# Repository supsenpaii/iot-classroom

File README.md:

# SmartClass

Giáo viên chiếu câu hỏi, học sinh bấm đáp án trên thiết bị ESP32-C3. Đáp án đi qua Wi-Fi/WebSocket, được lưu vào SQLite rồi máy chủ mới trả ACK, nên kết quả hiện lên web ngay lập tức.

<table>
<tr>
<td width="38%" valign="top">

**Nội dung**

1. [Kiến trúc hệ thống](#1-kiến-trúc-hệ-thống)
2. [Phần cứng](#2-phần-cứng)
   - [Linh kiện](#21-linh-kiện)
   - [Sơ đồ nguyên lý](#22-sơ-đồ-nguyên-lý)
   - [Mạch in PCB](#23-mạch-in-pcb)
   - [Mô hình 3D](#24-mô-hình-3d)
   - [Gán chân](#25-gán-chân)
   - [File thiết kế](#26-file-thiết-kế)
3. [Firmware ESP32](#3-firmware-esp32)
4. [Phần mềm Web](#4-phần-mềm-web)
5. [Giao thức & độ tin cậy](#5-giao-thức--độ-tin-cậy)
6. [Cài đặt & chạy](#6-cài-đặt--chạy)

</td>
<td width="62%" valign="top">

<p align="center"><sub>Thiết bị học sinh: ESP32-C3, PCB 2 lớp 50 × 80 mm, 13 phím, OLED 0,91"</sub></p>
</td>
</tr>
</table>

---

## 1. Kiến trúc hệ thống

| Thành phần | Công nghệ | Vai trò |
|---|---|---|
| Thiết bị học sinh | ESP32-C3-MINI-1-N4, bàn phím, OLED SSD1306 | Nhập ROOM ID + MSSV, gửi đáp án, hiện trạng thái |
| Backend | Node.js 24, Express 5, `ws` 8, SQLite (better-sqlite3) | Kiểm tra → lưu → ACK, máy trạng thái buổi thi |
| Frontend | React 19, Vite 8 | Bảng giáo viên, màn chiếu, báo cáo, `/student`, `/device` |
| AI ôn tập | Gemini (chính), OpenRouter (dự phòng) | Giải thích câu sai, sinh câu luyện thêm |

Học sinh không có thiết bị vẫn tham gia được bằng điện thoại qua `/student`, hoặc thiết bị ảo `/device`. Mọi nguồn đều dùng chung một đường WebSocket và một bộ luật chấm.

---

## 2. Phần cứng

PCB 2 lớp FR-4 1,6 mm, kích thước **50 × 80 mm**, 57 vị trí linh kiện, toàn bộ linh kiện ở mặt trên. ERC và DRC đều **0 lỗi**. Có 431 đoạn dây và 64 via. Dưới module ESP32 có 9 via tản nhiệt, cả hai mặt đổ đồng GND, chừa vùng cấm đồng dưới anten.

### 2.1 Linh kiện

| Khối | Linh kiện chính | Ghi chú |
|---|---|---|
| MCU | **ESP32-C3-MINI-1-N4** | RISC-V 160 MHz, Wi-Fi 2,4 GHz, BLE 5.0, flash 4 MB, anten PCB; USB Serial/JTAG có sẵn |
| Nguồn | 4 × AAA → **AMS1117-3.3** | Vin ≥ 4,3 V khi Wi-Fi phát (đỉnh ~350–400 mA) |
| Chọn nguồn / bảo vệ | **AO3401A** (P-MOS), **SS14**, **USBLC6-2SC6** | Chống ngược pin, tự ngắt pin khi cắm USB, chống ESD cho D+/D− |
| Giao tiếp | 13 phím 6×6 (0–9, OK, DEL, MODE), RESET/BOOT, SW1 MSS-22D18G2 | OLED 0,91" I²C qua header J3 |
| Báo hiệu | 3 LED 0805: nguồn / trạng thái / USB | Thụ động 0805 cho dễ hàn tay |

BOM đầy đủ: [`hardware/fabrication/IOT_BOM_V2.csv`](hardware/fabrication/IOT_BOM_V2.csv) (57 vị trí, cần mua 51 linh kiện).

### 2.2 Sơ đồ nguyên lý

<table>
<tr>
<td width="50%"><br><b>① Nguồn vào & bảo vệ.</b> Pin → SW1 → Q1 → VSYS. Cực G của Q1 nối VBUS: cắm USB thì Q1 ngắt, nguồn đi qua D1.</td>
<td width="50%"><br><b>② Ổn áp 3,3 V.</b> AMS1117-3.3. Ngõ ra dùng tụ tantalum 22 µF (cần ESR đủ lớn để LDO ổn định). LED D2 báo nguồn.</td>
</tr>
<tr>
<td><br><b>③ USB-C.</b> CC1/CC2 qua 5,1 kΩ; D+/D− qua 22 Ω và USBLC6 tới IO19/IO18 để nạp firmware và xem log.</td>
<td><br><b>④ MCU.</b> EN có RC 10 kΩ / 1 µF + nút RESET; IO9 + nút BOOT. Chân strapping IO2, IO8 được kéo lên.</td>
</tr>
<tr>
<td><br><b>⑤ Bàn phím.</b> Ma trận 4 hàng × 3 cột cho 12 phím, MODE nối riêng → 13 phím chỉ tốn 8 GPIO.</td>
<td><br><b>⑥ OLED / LED / đo pin.</b> I²C IO4/IO5 kéo lên 4,7 kΩ; LED trạng thái IO8; cầu chia 200k/100k đưa vào ADC IO3.</td>
</tr>
</table>

### 2.3 Mạch in PCB

<table>
<tr>
<td align="center" width="25%"><br><sub>F.Cu + in lụa</sub></td>
<td align="center" width="25%"><br><sub>B.Cu (lật gương)</sub></td>
<td align="center" width="25%"><br><sub>Đi dây 2 lớp</sub></td>
<td align="center" width="25%"><br><sub>Bản vẽ lắp ráp</sub></td>
</tr>
</table>

<p align="center"><br><sub>Kích thước mạch (mm): bo góc R4, lỗ M3 cách mép 4 mm</sub></p>

Thông số đi dây: tín hiệu 0,25 mm, nguồn 0,4–0,5 mm, chân ESP32/USB 0,2 mm; khe hở tối thiểu 0,2 mm; via 0,6/0,3 mm. Thông số đặt xưởng: 2 lớp, đồng 1 oz, mạ **ENIG**, phủ xanh chữ trắng, kèm stencil.

### 2.4 Mô hình 3D

<table>
<tr>
<td align="center" width="50%"><br><sub>Mặt trên</sub></td>
<td align="center" width="50%"><br><sub>Mặt dưới, có logo HCMUTE</sub></td>
</tr>
<tr>
<td align="center"><br><sub>ESP32-C3, AMS1117, header OLED</sub></td>
<td align="center"><br><sub>RESET/BOOT, công tắc SW1, USB-C</sub></td>
</tr>
</table>

### 2.5 Gán chân

Firmware hiện chạy trên **bản mẫu** (bo ESP32-C3 cắm USB + bàn phím 4×4 rời). Muốn dùng cho mạch PCB thì phải đổi bảng chân:

| Chức năng | Bản mẫu (firmware hiện tại) | Mạch PCB |
|---|---|---|
| Bàn phím | 4×4: hàng GPIO9, 10, 20, 21 · cột GPIO8, 7, 6, 5 | 4×3 + MODE: hàng IO0, IO1, IO2, IO10 · cột IO6, IO7, IO21 · MODE IO20 |
| Phím A–D | Phím riêng | MODE chuyển sang chế độ chữ |
| OLED I²C | SDA GPIO0, SCL GPIO1 | SDA IO4, SCL IO5 (kéo lên 4,7 kΩ) |
| LED / đo pin | — | LED IO8 · ADC IO3 |
| Nguồn | USB | 4×AAA hoặc USB-C |

### 2.6 File thiết kế

```
hardware/
├── kicad/                 # Project KiCad 10: mở IOT.kicad_pro
│   ├── IOT.kicad_sch / IOT.kicad_pcb / IOT.kicad_sym
│   ├── IOT.pretty/        # footprint riêng (ESP32-C3-MINI-1, MSS-22D18G2, nút 3×4)
│   └── 3dmodels/          # STEP (đường dẫn ${KIPRJMOD})
├── fabrication/           # Gerber .zip, BOM .csv/.xlsx, sơ đồ lắp ráp, bản in 1:1, hướng dẫn đặt mạch
└── Schematic_PCB.pdf      # Ảnh chi tiết sơ đồ, PCB, 3D (7 trang)
```

---

## 3. Firmware ESP32

`firmware/esp32-classroom/`: PlatformIO + Arduino, board `esp32-c3-devkitm-1`, USB CDC. Thư viện: ArduinoWebsockets, ArduinoJson 7, Adafruit SSD1306, Preferences (NVS).

```bash
cp firmware/esp32-classroom/include/device_config.example.h firmware/esp32-classroom/include/device_config.h
# điền Wi-Fi, DEVICE_ID/SECRET (lấy ở web: Thiết bị → Đăng ký), WS_HOST = IP máy chạy backend
pio run -d firmware/esp32-classroom -t upload
pio device monitor -d firmware/esp32-classroom
```

| Trạng thái OLED | Ý nghĩa |
|---|---|
| `ROOM ID + ENTER` → `STUDENT ID + ENTER` | Nhập mã phòng 8 số, rồi MSSV (1–10 số) |
| `READY / WAITING` | Đã ghép, chờ giáo viên bắt đầu |
| `QUIZ IN PROGRESS · Q 2/10 10s` | Đếm ngược theo giờ máy chủ |
| `SENDING: A` → `SAVED: A` | Chờ ACK → máy chủ đã lưu |
| `ATTENDANCE` / `QUICK POLL` / `FLASHCARD i/n` | Điểm danh (A), khảo sát (A–x), flashcard (A = nhớ, B = chưa nhớ) |

Các cơ chế chính:
- Chống dội phím 40 ms. Mỗi lần bấm chỉ tạo một sự kiện.
- Heartbeat 4 giây.
- Gói chưa nhận ACK được lưu NVS và gửi lại mỗi 1,2 giây, giữ nguyên `request_id`.
- OLED tự tắt khi rảnh (60/20/30 giây), nhưng luôn sáng trong lúc làm bài.

---

## 4. Phần mềm Web

<table>
<tr>
<td width="50%"><br><b>Phòng chờ.</b> ROOM ID 8 số, hiệu lực 5 phút. Thiết bị gửi MSSV để ghép đúng học sinh (10/10 đã kết nối).</td>
<td width="50%"><br><b>Điều khiển buổi thi.</b> Câu hiện tại, thời gian còn lại, số đáp án đã lưu, đóng câu / tạm dừng.</td>
</tr>
<tr>
<td><br><b>Màn chiếu.</b> Câu hỏi và 4 lựa chọn theo màu/hình; công bố phân bố đáp án sau khi đóng câu.</td>
<td><br><b>Thiết bị ảo <code>/device</code>.</b> Mô phỏng OLED 128×32 + bàn phím, hành vi giống firmware (READY → SAVED).</td>
</tr>
<tr>
<td><br><b>Báo cáo.</b> Điểm trung bình, tỷ lệ đạt, ma trận học sinh × câu, xuất Excel/PDF.</td>
<td><br><b>Thống kê.</b> Phổ điểm, xếp loại, độ khó, độ phân biệt, thời gian trả lời từng câu.</td>
</tr>
<tr>
<td><br><b>Quản lý thiết bị.</b> Đăng ký, đổi tên, cấp lại secret, thu hồi.</td>
<td><br><b>Đổi tên thiết bị.</b> Chỉ đổi nhãn quản lý; ID, secret, kết nối và báo cáo cũ giữ nguyên.</td>
</tr>
</table>

| Nhóm | Chức năng |
|---|---|
| Lớp & đề | Nhập học sinh/câu hỏi từ XLSX/CSV (xem trước, sửa lỗi), ngân hàng câu hỏi theo chủ đề |
| Buổi thi | 1–100 câu, 5–300 s/câu, trộn câu, tự chuyển, cho đổi đáp án, thi đua top 5; LOBBY → RUNNING ⇄ PAUSED → FINISHED |
| Báo cáo | Điểm = đúng ÷ câu tính điểm × 10; xếp loại; KR-20; loại câu và tính lại; nhập kết quả cũ |
| Hoạt động thêm | Flashcard (cả lớp + link tự học `/study/<mã>`), khảo sát nhanh ẩn danh, điểm danh 1 phím |
| AI | Giải chi tiết câu sai + câu luyện thêm; chỉ gửi nội dung đề, không gửi tên/MSSV |
| Khác | Giao diện VI/EN đổi tại chỗ, sáng/tối, dùng được trên điện thoại |

<p align="center"><br><sub>Luồng gợi ý ôn tập bằng AI</sub></p>

---

## 5. Giao thức & độ tin cậy

```json
{ "v": 1, "type": "answer.submit", "request_id": "uuid-moi-lan-doi-dap-an",
  "session_id": "...", "question_instance_id": "...", "binding_id": "...", "seq": 1, "choice": "B" }
```

- `SAVED` chỉ hiện khi đã nhận `answer.ack`. Mất ACK thì gửi lại nguyên gói; máy chủ trả lại ACK cũ, không ghi trùng.
- Mỗi lần đổi đáp án thì tăng `seq`, nên gói cũ không thể đè lên lựa chọn mới. Hạn giờ do máy chủ quyết định.
- Lệnh của giáo viên kèm `command_id` + `expected_version` để chống bấm lặp (trả HTTP 409 nếu xung đột).
- Máy chủ khởi động lại thì buổi đang chạy chuyển sang `PAUSED`, đáp án đã ACK còn nguyên.
- Bảo mật: mật khẩu băm scrypt, cookie HttpOnly, CSRF, kiểm tra Origin, phiên học sinh tách riêng, giới hạn tốc độ đăng nhập/vào phòng.

<p align="center"><br><sub>Trình tự một phiên: ghép phòng (HTTP) → WebSocket → thi → báo cáo</sub></p>

---

## 6. Cài đặt & chạy

Yêu cầu **Node 24.21+**.

```bash
npm ci
npm run build
cp .env.example .env          # điền SESSION_SECRET:
node -e "console.log(require('crypto').randomBytes(48).toString('hex'))"
npm run db:migrate
npm start                     # http://localhost:3000/register
```

**Demo không cần phần cứng.** Đặt `ENABLE_SIMULATOR=true`, chạy `npm run demo:create -- <email-giao-vien>` (lúc app đang dừng) để tạo lớp 10 học sinh, đề 10 câu và phòng chờ. Sau đó mở phòng → **Mở nhận thiết bị**, rồi vào phòng bằng `/simulator`, `/device` hoặc `/student`.

**ESP32 trong mạng LAN.** Đặt `HOST=0.0.0.0` và `PUBLIC_ORIGIN=http://<IP-LAN>:3000`. Trong `device_config.h` của firmware, đặt `WS_HOST=<IP-LAN>`. Không dùng `localhost` cho ESP32. ESP32-C3 chỉ hỗ trợ Wi-Fi **2,4 GHz**.

**Truy cập từ xa.** Dùng Tailscale Funnel hoặc `deploy/` (Docker + Caddy HTTPS/WSS). Khi chạy sau proxy, bắt buộc đặt `TRUST_PROXY=1`.

| Biến `.env` | Ý nghĩa |
|---|---|
| `SESSION_SECRET` | Bắt buộc, ≥ 32 ký tự ngẫu nhiên |
| `PUBLIC_ORIGIN` | Đúng địa chỉ trình duyệt mở, không có `/` ở cuối |
| `DATABASE_PATH` | File SQLite (mặc định `./data/app.sqlite`) |
| `GEMINI_API_KEY` / `OPENROUTER_API_KEYS` | Bật tính năng AI ôn tập (chỉ lưu ở server) |

Vận hành: `npm run db:backup`, `npm run db:restore -- <file> --confirm-replace`, `npm run teacher:reset-password`.

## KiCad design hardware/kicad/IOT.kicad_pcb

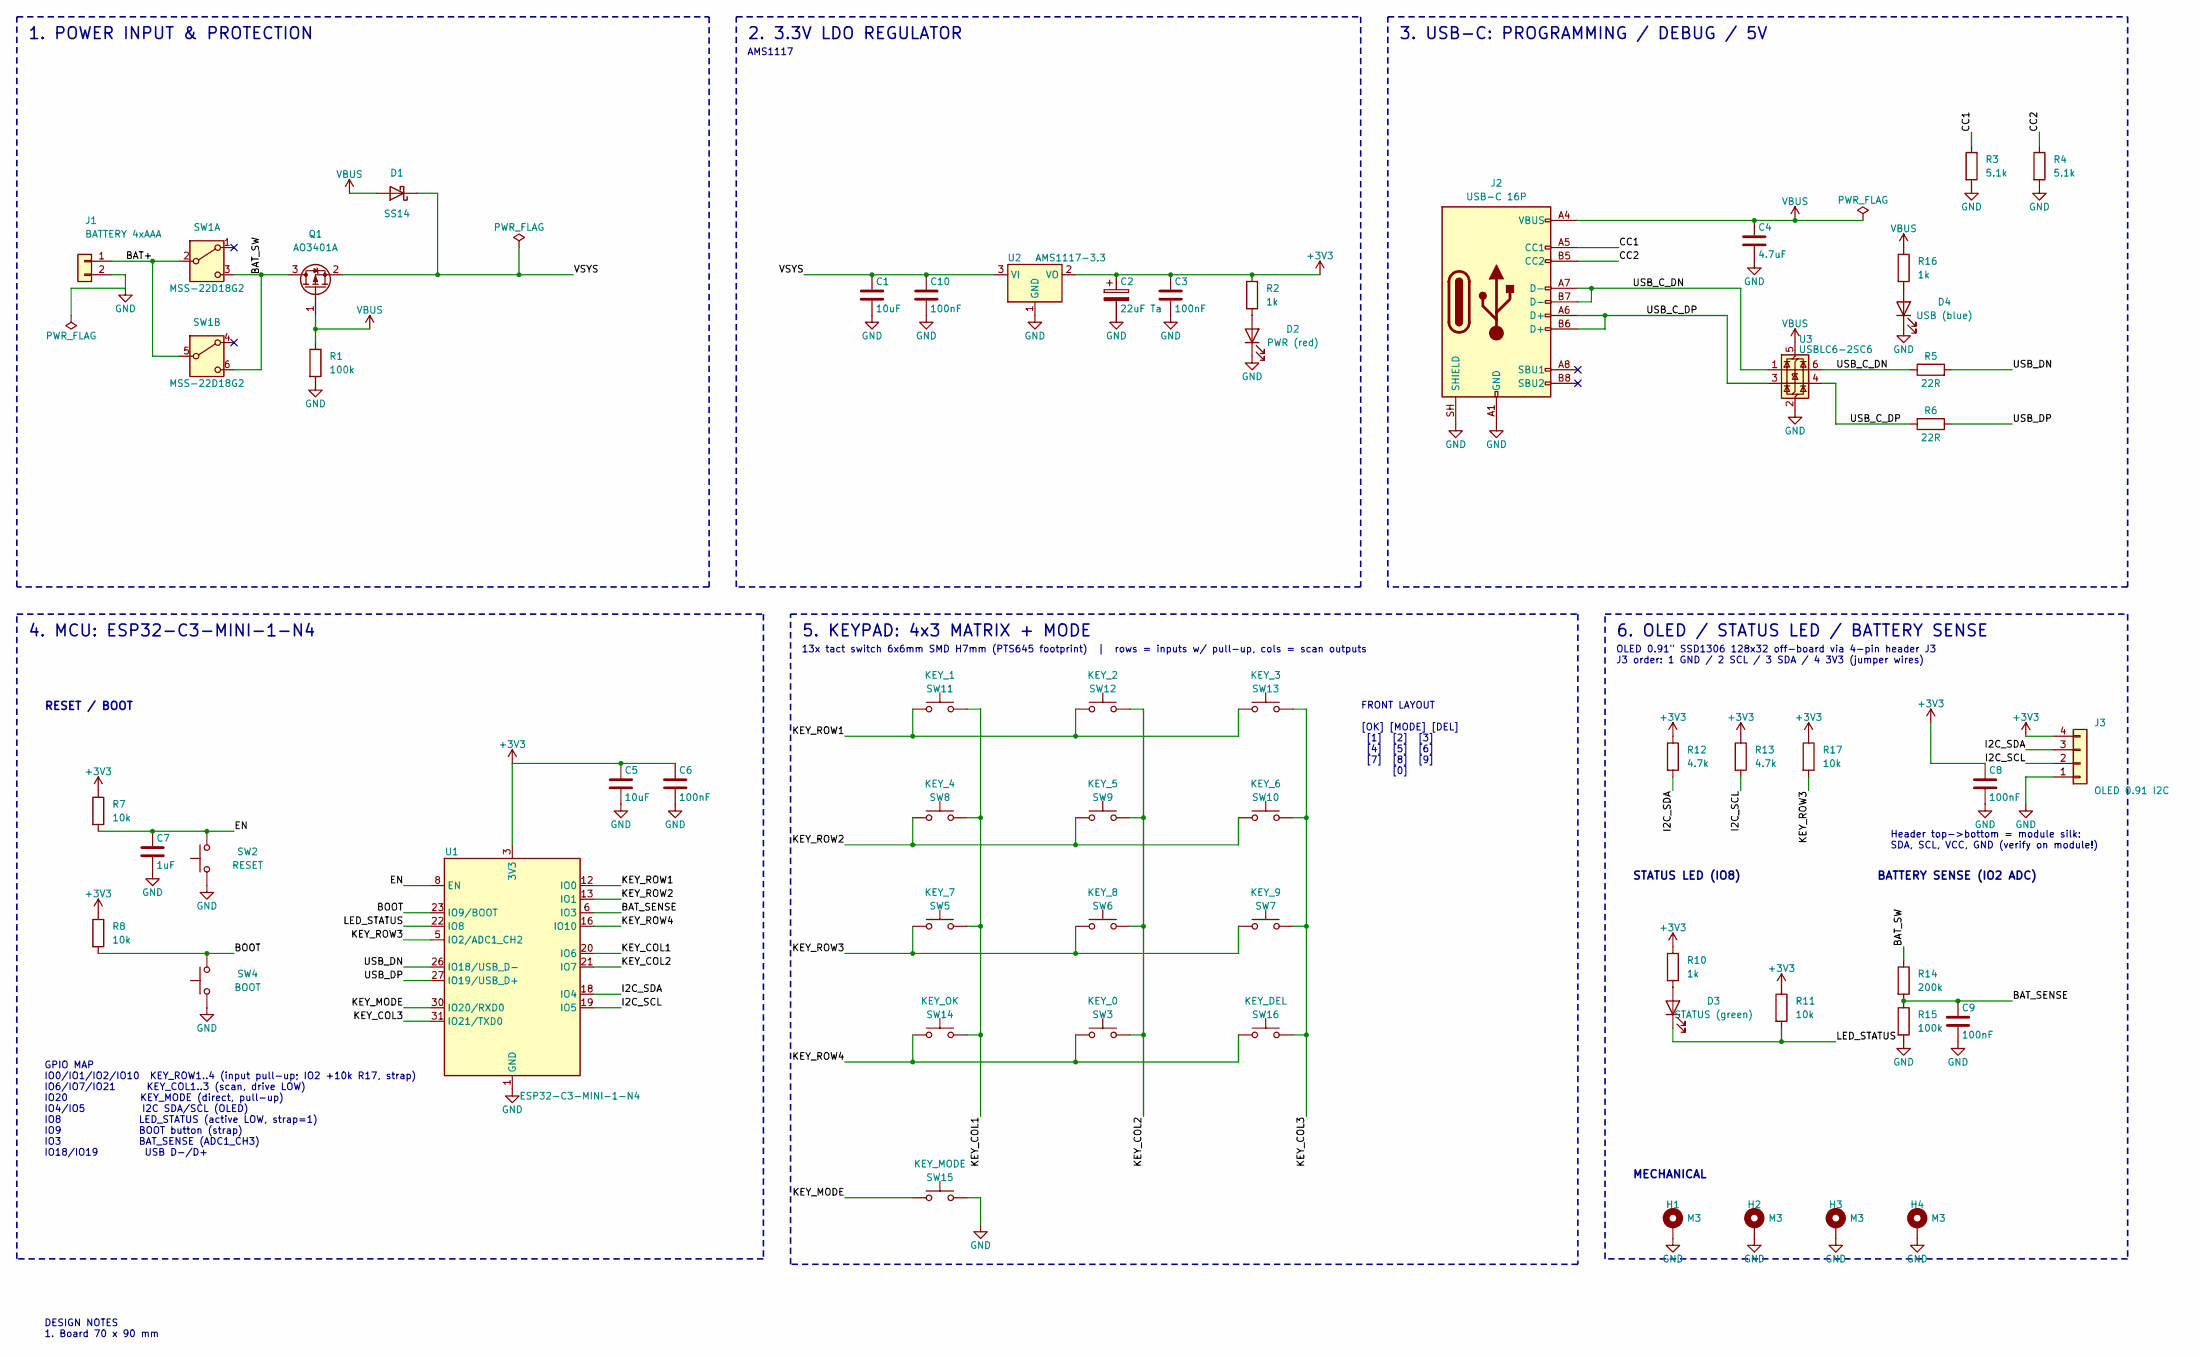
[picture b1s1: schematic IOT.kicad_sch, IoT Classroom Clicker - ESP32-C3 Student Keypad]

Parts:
C1, C5: 10uF; C_0805_2012Metric
C2: 22uF Ta; CP_EIA-3528-21_Kemet-B
C3, C6, C8, C9, C10: 100nF; C_0805_2012Metric
C4: 4.7uF; C_0805_2012Metric
C7: 1uF; C_0805_2012Metric
D1: SS14; D_SMA
D2: PWR (red); LED_0805_2012Metric
D3: STATUS (green); LED_0805_2012Metric
D4: USB (blue); LED_0805_2012Metric
H1, H2, H3, H4: M3; MountingHole_3.2mm_M3_Pad_Via
J1: BATTERY 4xAAA; PinHeader_1x02_P2.54mm_Vertical
J2: USB-C 16P; USB_C_Receptacle_HRO_TYPE-C-31-M-12
J3: OLED 0.91 I2C; PinHeader_1x04_P2.54mm_Vertical
Q1: AO3401A; SOT-23
R1, R15: 100k; R_0805_2012Metric
R2, R10, R16: 1k; R_0805_2012Metric
R3, R4: 5.1k; R_0805_2012Metric
R5, R6: 22R; R_0805_2012Metric
R7, R8, R11, R17: 10k; R_0805_2012Metric
R12, R13: 4.7k; R_0805_2012Metric
R14: 200k; R_0805_2012Metric
SW1: MSS-22D18G2; SW_DPDT_MSS-22D18G2
SW2: RESET; SW_SPST_3x4mm_2P
SW3: KEY_0; SW_SPST_PTS645Sx43SMTR92
SW4: BOOT; SW_SPST_3x4mm_2P
SW5: KEY_7; SW_SPST_PTS645Sx43SMTR92
SW6: KEY_8; SW_SPST_PTS645Sx43SMTR92
SW7: KEY_9; SW_SPST_PTS645Sx43SMTR92
SW8: KEY_4; SW_SPST_PTS645Sx43SMTR92
SW9: KEY_5; SW_SPST_PTS645Sx43SMTR92
SW10: KEY_6; SW_SPST_PTS645Sx43SMTR92
SW11: KEY_1; SW_SPST_PTS645Sx43SMTR92
SW12: KEY_2; SW_SPST_PTS645Sx43SMTR92
SW13: KEY_3; SW_SPST_PTS645Sx43SMTR92
SW14: KEY_OK; SW_SPST_PTS645Sx43SMTR92
SW15: KEY_MODE; SW_SPST_PTS645Sx43SMTR92
SW16: KEY_DEL; SW_SPST_PTS645Sx43SMTR92
U1: ESP32-C3-MINI-1-N4
U2: AMS1117-3.3; SOT-223-3_TabPin2
U3: USBLC6-2SC6; SOT-23-6

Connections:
+3V3: C2.1, C3.1, C5.1, C6.1, C8.1, J3.4, R2.1, R7.1, R8.1, R10.1, R11.1, R12.1, R13.1, R17.1, U1.3 (3V3), U2.2 (VO)
/BAT+: J1.1, SW1.2 (B), SW1.5 (B)
/BAT_SENSE: C9.1, R14.2, R15.1, U1.6 (IO3)
/BAT_SW: Q1.3 (D), R14.1, SW1.3 (C), SW1.6 (C)
/BOOT: R8.2, SW4.2, U1.23 (IO9/BOOT)
/CC1: J2.A5 (CC1), R3.1
/CC2: J2.B5 (CC2), R4.1
/EN: C7.1, R7.2, SW2.2, U1.8 (EN)
/I2C_SCL: J3.2, R13.2, U1.19 (IO5)
/I2C_SDA: J3.3, R12.2, U1.18 (IO4)
/KEY_COL1: SW5.2, SW8.2, SW11.2, SW14.2, U1.20 (IO6)
/KEY_COL2: SW3.2, SW6.2, SW9.2, SW12.2, U1.21 (IO7)
/KEY_COL3: SW7.2, SW10.2, SW13.2, SW16.2, U1.31 (IO21/TXD0)
/KEY_MODE: SW15.1, U1.30 (IO20/RXD0)
/KEY_ROW1: SW11.1, SW12.1, SW13.1, U1.12 (IO0)
/KEY_ROW2: SW8.1, SW9.1, SW10.1, U1.13 (IO1)
/KEY_ROW3: R17.2, SW5.1, SW6.1, SW7.1, U1.5 (IO2/ADC1_CH2)
/KEY_ROW4: SW3.1, SW14.1, SW16.1, U1.16 (IO10)
/LED_STATUS: D3.1 (K), R11.2, U1.22 (IO8)
/USB_C_DN: J2.A7 (D-), J2.B7 (D-), R5.1, U3.1 (I/O1), U3.6 (I/O1)
/USB_C_DP: J2.A6 (D+), J2.B6 (D+), R6.1, U3.3 (I/O2), U3.4 (I/O2)
/USB_DN: R5.2, U1.26 (IO18/USB_D-)
/USB_DP: R6.2, U1.27 (IO19/USB_D+)
/VSYS: C1.1, C10.1, D1.1 (K), Q1.2 (S), U2.3 (VI)
GND: C1.2, C2.2, C3.2, C4.2, C5.2, C6.2, C7.2, C8.2, C9.2, C10.2, D2.1 (K), D4.1 (K), H1.1, H2.1, H3.1, H4.1, J1.2, J2.A1 (GND), J2.A12 (GND), J2.B1 (GND), J2.B12 (GND), J2.SH (SHIELD), J3.1, R1.2, R3.2, R4.2, R15.2, SW2.1, SW4.1, SW15.2, U1.1 (GND), U1.2 (GND), U1.11 (GND), U1.14 (GND), U1.36 (GND), U1.37 (GND), U1.38 (GND), U1.39 (GND), U1.40 (GND), U1.41 (GND), U1.42 (GND), U1.43 (GND), U1.44 (GND), U1.45 (GND), U1.46 (GND), U1.47 (GND), U1.48 (GND), U1.49_1 (GND), U1.49_2 (GND), U1.49_3 (GND), U1.49_4 (GND), U1.49_5 (GND), U1.49_6 (GND), U1.49_7 (GND), U1.49_8 (GND), U1.49_9 (GND), U1.50 (GND), U1.51 (GND), U1.52 (GND), U1.53 (GND), U2.1 (GND), U3.2 (GND)
unnamed: D2.2 (A), R2.2
unnamed: D3.2 (A), R10.2
unnamed: D4.2 (A), R16.2
VBUS: C4.1, D1.2 (A), J2.A4 (VBUS), J2.A9 (VBUS), J2.B4 (VBUS), J2.B9 (VBUS), Q1.1 (G), R1.1, R16.1, U3.5 (VBUS)

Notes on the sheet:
RESET / BOOT
3. USB-C: PROGRAMMING / DEBUG / 5V
13x tact switch 6x6mm SMD H7mm (PTS645 footprint) | rows = inputs w/ pull-up, cols = scan outputs
1. POWER INPUT & PROTECTION
OLED 0.91" SSD1306 128x32 off-board via 4-pin header J3 J3 order: 1 GND / 2 SCL / 3 SDA / 4 3V3 (jumper wires)
MECHANICAL
4. MCU: ESP32-C3-MINI-1-N4
STATUS LED (IO8)
GPIO MAP IO0/IO1/IO2/IO10 KEY_ROW1..4 (input pull-up; IO2 +10k R17, strap) IO6/IO7/IO21 KEY_COL1..3 (scan, drive LOW) IO20 KEY_MODE (direct, pull-up) IO4/IO5 I2C SDA/SCL (OLED) IO8 LED_STATUS (active LOW, strap=1) IO9 BOOT button (strap) IO3 BAT_SENSE (ADC1_CH3) IO18/IO19 USB D-/D+
Header top->bottom = module silk: SDA, SCL, VCC, GND (verify on module!)
FRONT LAYOUT [OK] [MODE] [DEL] [1] [2] [3] [4] [5] [6] [7] [8] [9] [0]
DESIGN NOTES 1. Board 70 x 90 mm
5. KEYPAD: 4x3 MATRIX + MODE
2. 3.3V LDO REGULATOR
6. OLED / STATUS LED / BATTERY SENSE
AMS1117
BATTERY SENSE (IO2 ADC)

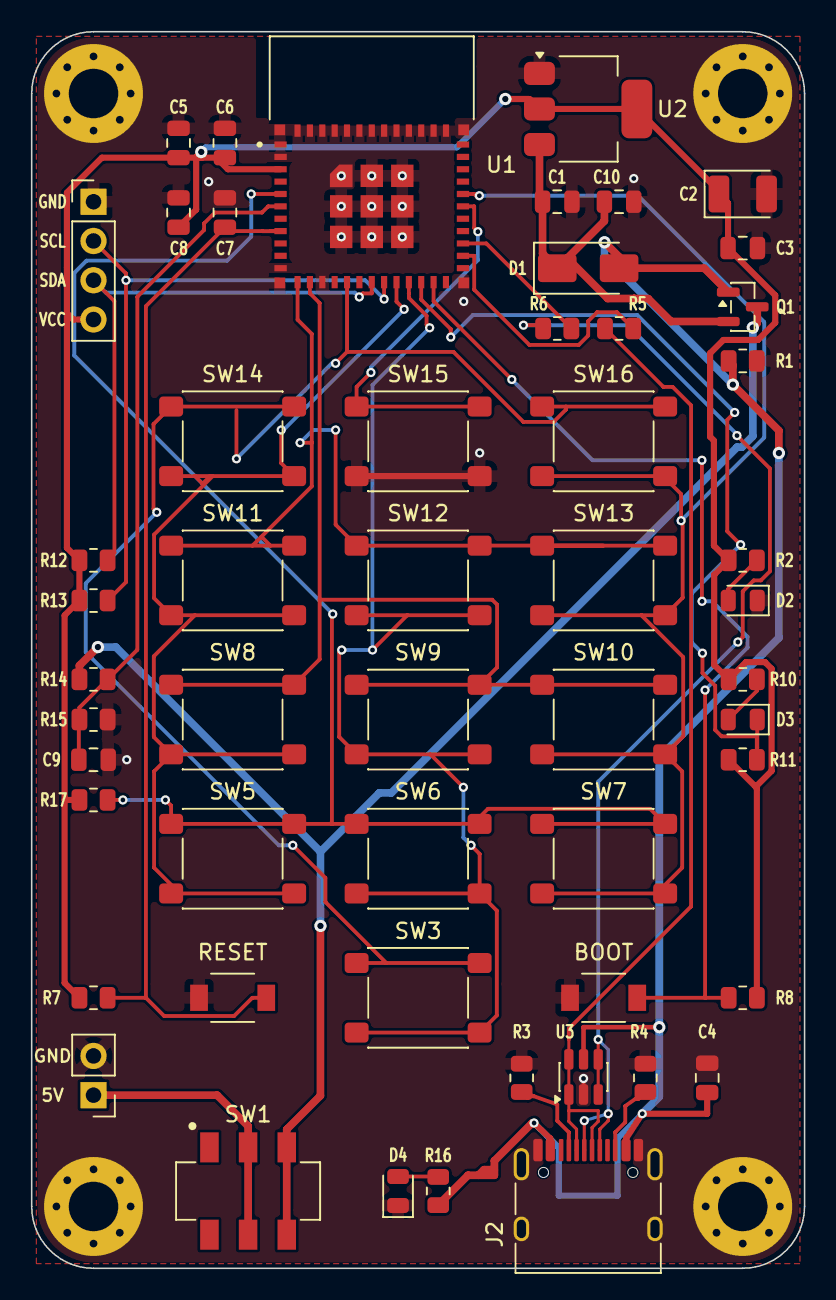
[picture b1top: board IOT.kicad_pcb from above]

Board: 2 copper layers, 50.0 x 80.0 mm, 57 parts (0 on the bottom side), 29 nets.

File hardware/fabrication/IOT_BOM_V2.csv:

Reference,Qty,Value,Footprint,Link,Note,Datasheet
,,,,,,
Thế Giới IC ,,,,,,
"C1,C5",2,10uF,Capacitor_SMD:C_0805_2012Metric,https://www.thegioiic.com/tu-gom-0805-10uf-16v,Tụ Gốm 0805 10uF 16V,
"C3,C6,C8,C9,C10",5,100nF,Capacitor_SMD:C_0805_2012Metric,https://www.thegioiic.com/tu-gom-0805-100nf-0-1uf-50v,Tụ Gốm 0805 100nF (0.1uF) 50V,
C4,1,4.7uF,Capacitor_SMD:C_0805_2012Metric,https://www.thegioiic.com/tu-gom-0805-4-7uf-50v,Tụ Gốm 0805 4.7uF 50V,
C7,1,1uF,Capacitor_SMD:C_0805_2012Metric,https://www.thegioiic.com/tu-gom-0805-1uf-16v,Tụ Gốm 0805 1uF 16V,
D1,1,SS14,Diode_SMD:D_SMA,https://www.thegioiic.com/ss14-sma-diode-schottky-1a-1n5819,SS14 SMA Diode Schottky 1A 1N5819,https://www.vishay.com/docs/88746/ss12.pdf
D2,1,PWR (red),LED_SMD:LED_0805_2012Metric,https://www.thegioiic.com/led-do-0805-dan-smd-trong-suot,LED Đỏ 0805 Dán SMD Trong Suốt,
D3,1,STATUS (green),LED_SMD:LED_0805_2012Metric,https://www.thegioiic.com/led-xanh-la-0805-dan-smd-trong-suot,LED Xanh Lá 0805 Dán SMD Trong Suốt,
D4,1,USB (blue),LED_SMD:LED_0805_2012Metric,https://www.thegioiic.com/led-xanh-duong-0805-dan-smd-trong-suot,LED Xanh Dương 0805 Dán SMD Trong Suốt (báo cắm cáp USB-C),
J2,1,USB-C 16P,Connector_USB:USB_C_Receptacle_HRO_TYPE-C-31-M-12,https://www.thegioiic.com/cong-usb-cai-3-1-type-c-16-chan-th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,Cổng USB Cái 3.1 Type C 16 Chân Thẳng Dán SMD,https://www.usb.org/sites/default/files/documents/usb_type-c.zip
Q1,1,AO3401A,Package_TO_SOT_SMD:SOT-23,https://www.thegioiic.com/ao3401a-mosfet-kenh-p-30v-4a-sot23,AO3401A MOSFET Kênh P 30V 4A SOT23,http://www.aosmd.com/pdfs/datasheet/AO3401A.pdf
"R1,R15",2,100k,Resistor_SMD:R_0805_2012Metric,https://www.thegioiic.com/dien-tro-100-kohm-0805-1-,Điện Trở 100 KOhm 0805 1%,
"R2,R10,R16",3,1k,Resistor_SMD:R_0805_2012Metric,https://www.thegioiic.com/dien-tro-1-kohm-0805-5-,Điện Trở 1 KOhm 0805 5%,
"R3,R4",2,5.1k,Resistor_SMD:R_0805_2012Metric,https://www.thegioiic.com/dien-tro-5-1-kohm-0805-5-,Điện Trở 5.1 KOhm 0805 5%,
"R5,R6",2,22R,Resistor_SMD:R_0805_2012Metric,https://www.thegioiic.com/dien-tro-22-ohm-0805-5-,Điện Trở 22 Ohm 0805 5% (Khử nhiễu dùng 22 Ohm),
"R7,R8,R11,R17",4,10k,Resistor_SMD:R_0805_2012Metric,https://www.thegioiic.com/dien-tro-10-kohm-0805-5-,Điện Trở 10 KOhm 0805 5%,
"R12,R13",2,4.7k,Resistor_SMD:R_0805_2012Metric,https://www.thegioiic.com/dien-tro-4-7-kohm-0805-5-,Điện Trở 4.7 KOhm 0805 5%,
R14,1,200k,Resistor_SMD:R_0805_2012Metric,https://www.thegioiic.com/dien-tro-200-kohm-0805-1-,Điện Trở 200 KOhm 0805 1%,
SW1,1,MSS-22D18G2,IOT:SW_DPDT_MSS-22D18G2,https://www.thegioiic.com/mss-22d18g2-cong-tac-truot-6-chan-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,MSS-22D18G2 Công Tắc Trượt 6 Chân SMD 2P2T,
"SW2,SW4",2,"RESET, BOOT",IOT:SW_SPST_3x4mm_2P,https://www.thegioiic.com/nut-nhan-3x4mm-cao-2-5mm-2-chan-smd,"Nút nhấn 3x4mm cao 2.5mm 2 chân SMD — SW2 = RESET, SW4 = BOOT",
"SW3,SW5,SW6,SW7,SW8,SW9,SW10,SW11,SW12,SW13,SW14,SW15,SW16",13,"KEY (0-9, OK, MODE, DEL)",Button_Switch_SMD:SW_SPST_PTS645Sx43SMTR92,https://www.thegioiic.com/nut-nhan-6x6mm-cao-7mm-4-chan-smd,Nút nhấn 6x6mm cao 7mm 4 chân SMD — 13 phím bàn phím,
U2,1,AMS1117-3.3,Package_TO_SOT_SMD:SOT-223-3_TabPin2,https://www.thegioiic.com/ams1117-3-3v-ic-on-ap-3-3v-1a-sot-223,AMS1117-3.3V IC Ổn Áp 3.3V 1A SOT-223,http://www.advanced-monolithic.com/pdf/ds1117.pdf
,,,,,,
IC Đây Rồi ,,,,,,
C2,1,22uF Ta,Capacitor_Tantalum_SMD:CP_EIA-3528-21_Kemet-B,https://icdayroi.com/tu-tantalum-22uf-16v-smd3528,Tụ Tantalum 22uF 16V SMD3528,
U3,1,USBLC6-2SC6,Package_TO_SOT_SMD:SOT-23-6,https://icdayroi.com/usblc6-2sc6-tvs-diode-5-25v-17v-sot23-6,USBLC6-2SC6 TVS diode chống ESD cho USB 5.25V 17V SOT23-6,https://www.st.com/resource/en/datasheet/usblc6-2.pdf
,,,,,,
Điện Tử Tuyết Nga,,,,,,
U1,1,ESP32-C3-MINI-1-N4,IOT:ESP32-C3-MINI-1-N4,https://dientutuyetnga.com/products/thu-phat-wifi-esp32-c3-m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,Thu Phát Wifi ESP32-C3-Mini-1-N4 2.4Ghz BLE 5.0,https://www.espressif.com/sites/default/files/documentation/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
,,,,,,
Đã có,,,,,,
"H1,H2,H3,H4",4,M3,MountingHole:MountingHole_3.2mm_M3_Pad_Via,,"Lỗ vít M3 mạ đồng nối GND (làm sẵn trên PCB, không phải mua)",
J1,1,BATTERY 4xAAA,Connector_PinHeader_2.54mm:PinHeader_1x02_P2.54mm_Vertical,Header đã có,"Header đực 1x2 2.54mm — cắm dây hộp pin 4xAAA (đầu cái/jumper); chân vuông = 5V(+), chân tròn = GND",
J3,1,OLED 0.91 I2C,Connector_PinHeader_2.54mm:PinHeader_1x04_P2.54mm_Vertical,Header đã có,"Header đực 1x4 2.54mm — nối OLED 0.91"" bằng 4 dây jumper theo nhãn GND-SCL-SDA-VCC (không cắm thẳng module)",
,,,,,,
TỔNG,57,,,,57 vị trí linh kiện; cần mua 51 (trừ 4 lỗ M3 làm sẵn trên PCB và 2 header J1/J3 đã có),
